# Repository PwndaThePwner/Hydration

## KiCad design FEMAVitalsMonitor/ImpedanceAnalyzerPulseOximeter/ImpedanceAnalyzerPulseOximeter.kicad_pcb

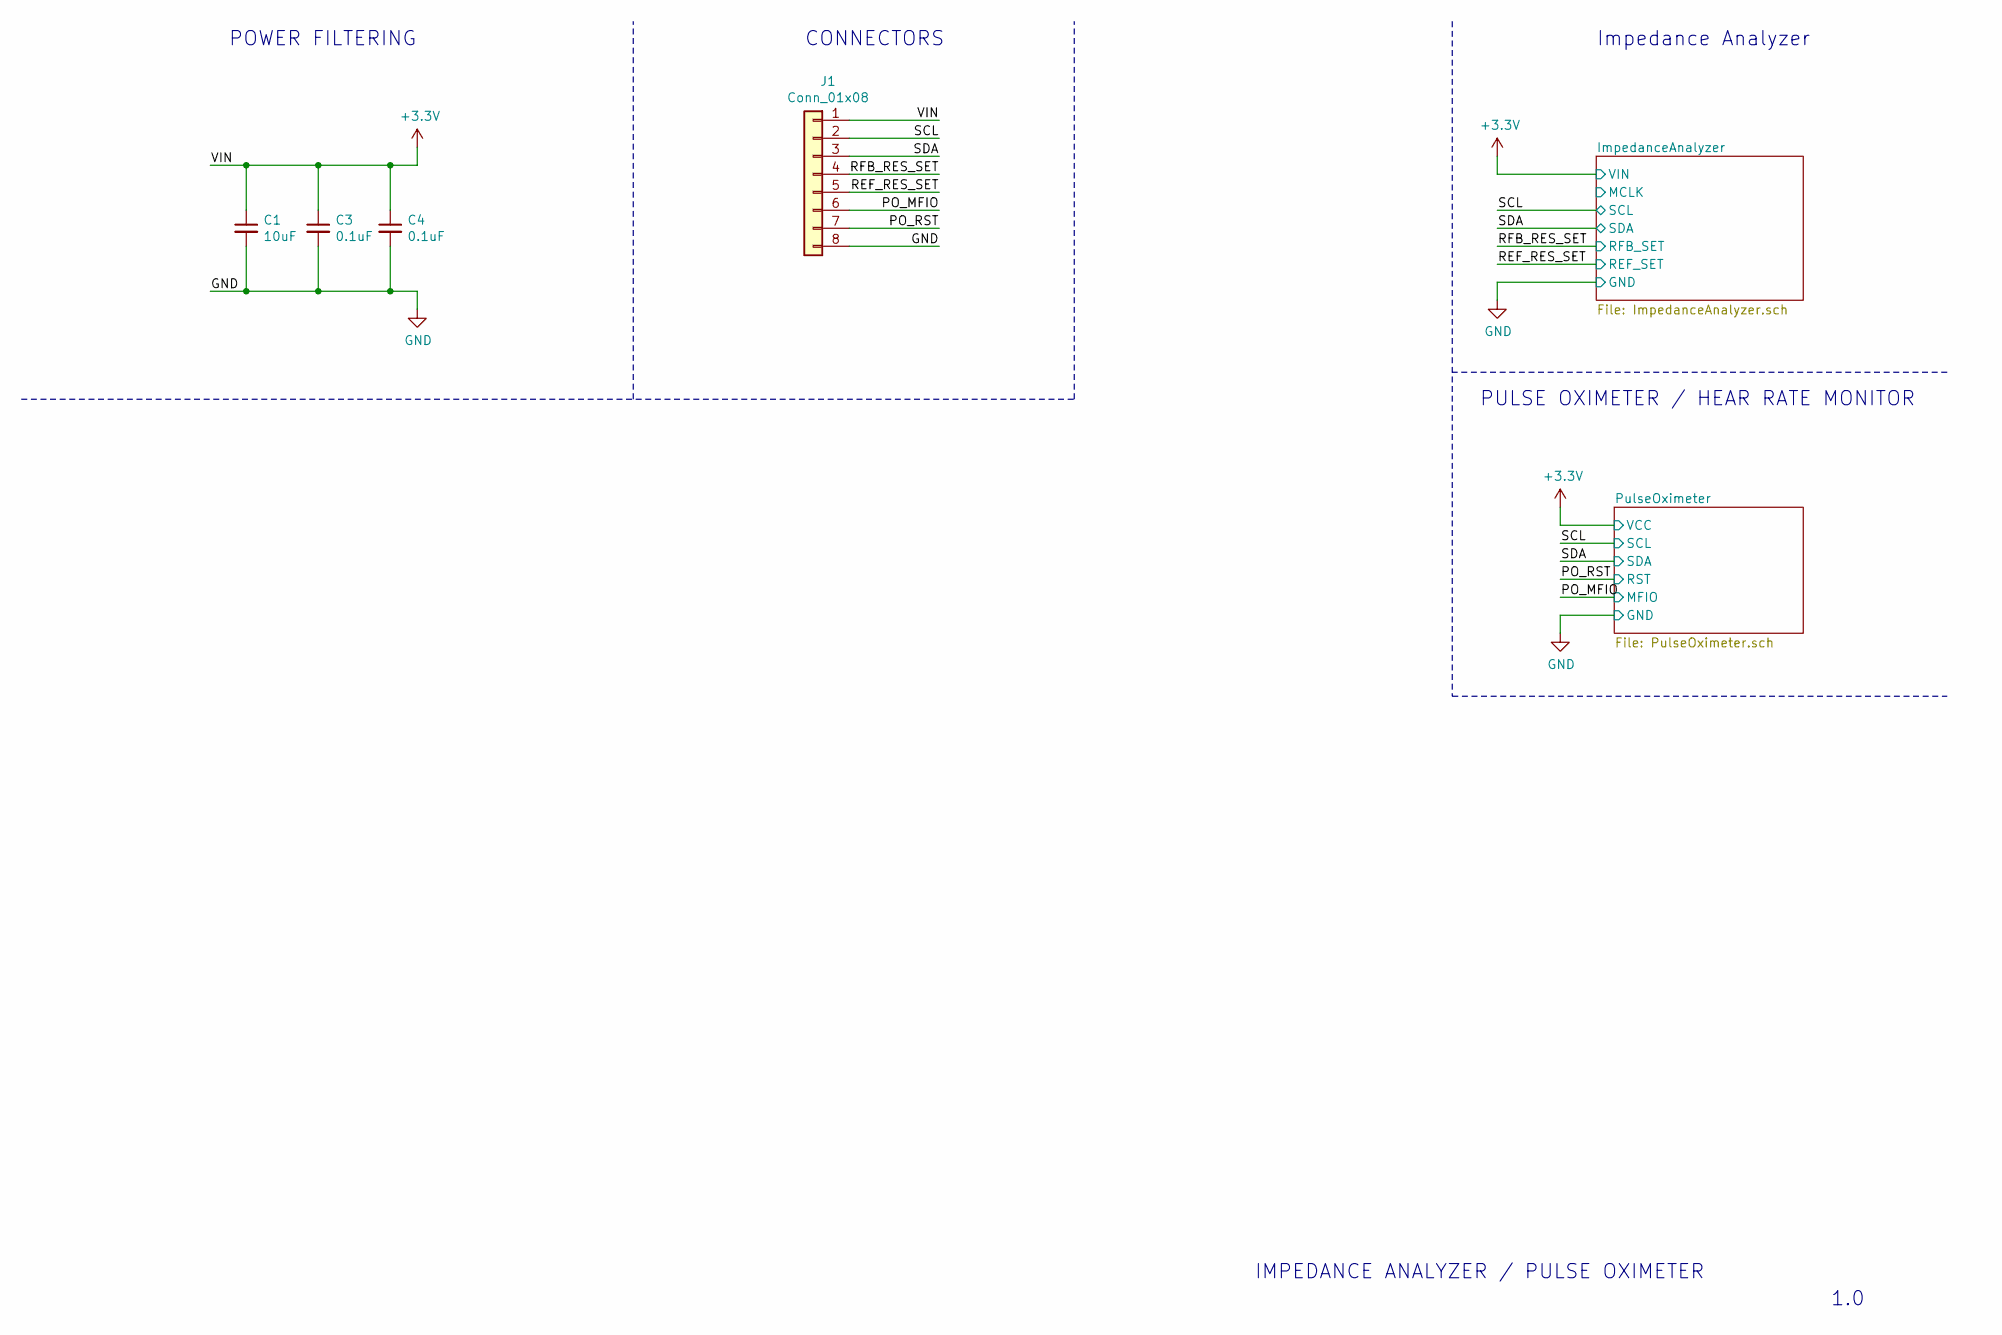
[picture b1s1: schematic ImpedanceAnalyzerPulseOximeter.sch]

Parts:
C1: 10uF; C_0805_2012Metric_Pad1.18x1.45mm_HandSolder
C3, C4: 0.1uF; C_0805_2012Metric_Pad1.18x1.45mm_HandSolder
J1: Conn_01x08; PinHeader_1x08_P2.54mm_Vertical

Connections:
+3V3: C1.1, C3.1, C4.1, J1.1; also elsewhere on the board
/PO_MFIO: J1.6; also elsewhere on the board
/PO_RST: J1.7; also elsewhere on the board
/REF_RES_SET: J1.5; also elsewhere on the board
/RFB_RES_SET: J1.4; also elsewhere on the board
/SCL: J1.2; also elsewhere on the board
/SDA: J1.3; also elsewhere on the board
GND: C1.2, C3.2, C4.2, J1.8; also elsewhere on the board

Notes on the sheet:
Impedance Analyzer
POWER FILTERING
PULSE OXIMETER / HEAR RATE MONITOR
CONNECTORS
IMPEDANCE ANALYZER / PULSE OXIMETER
1.0

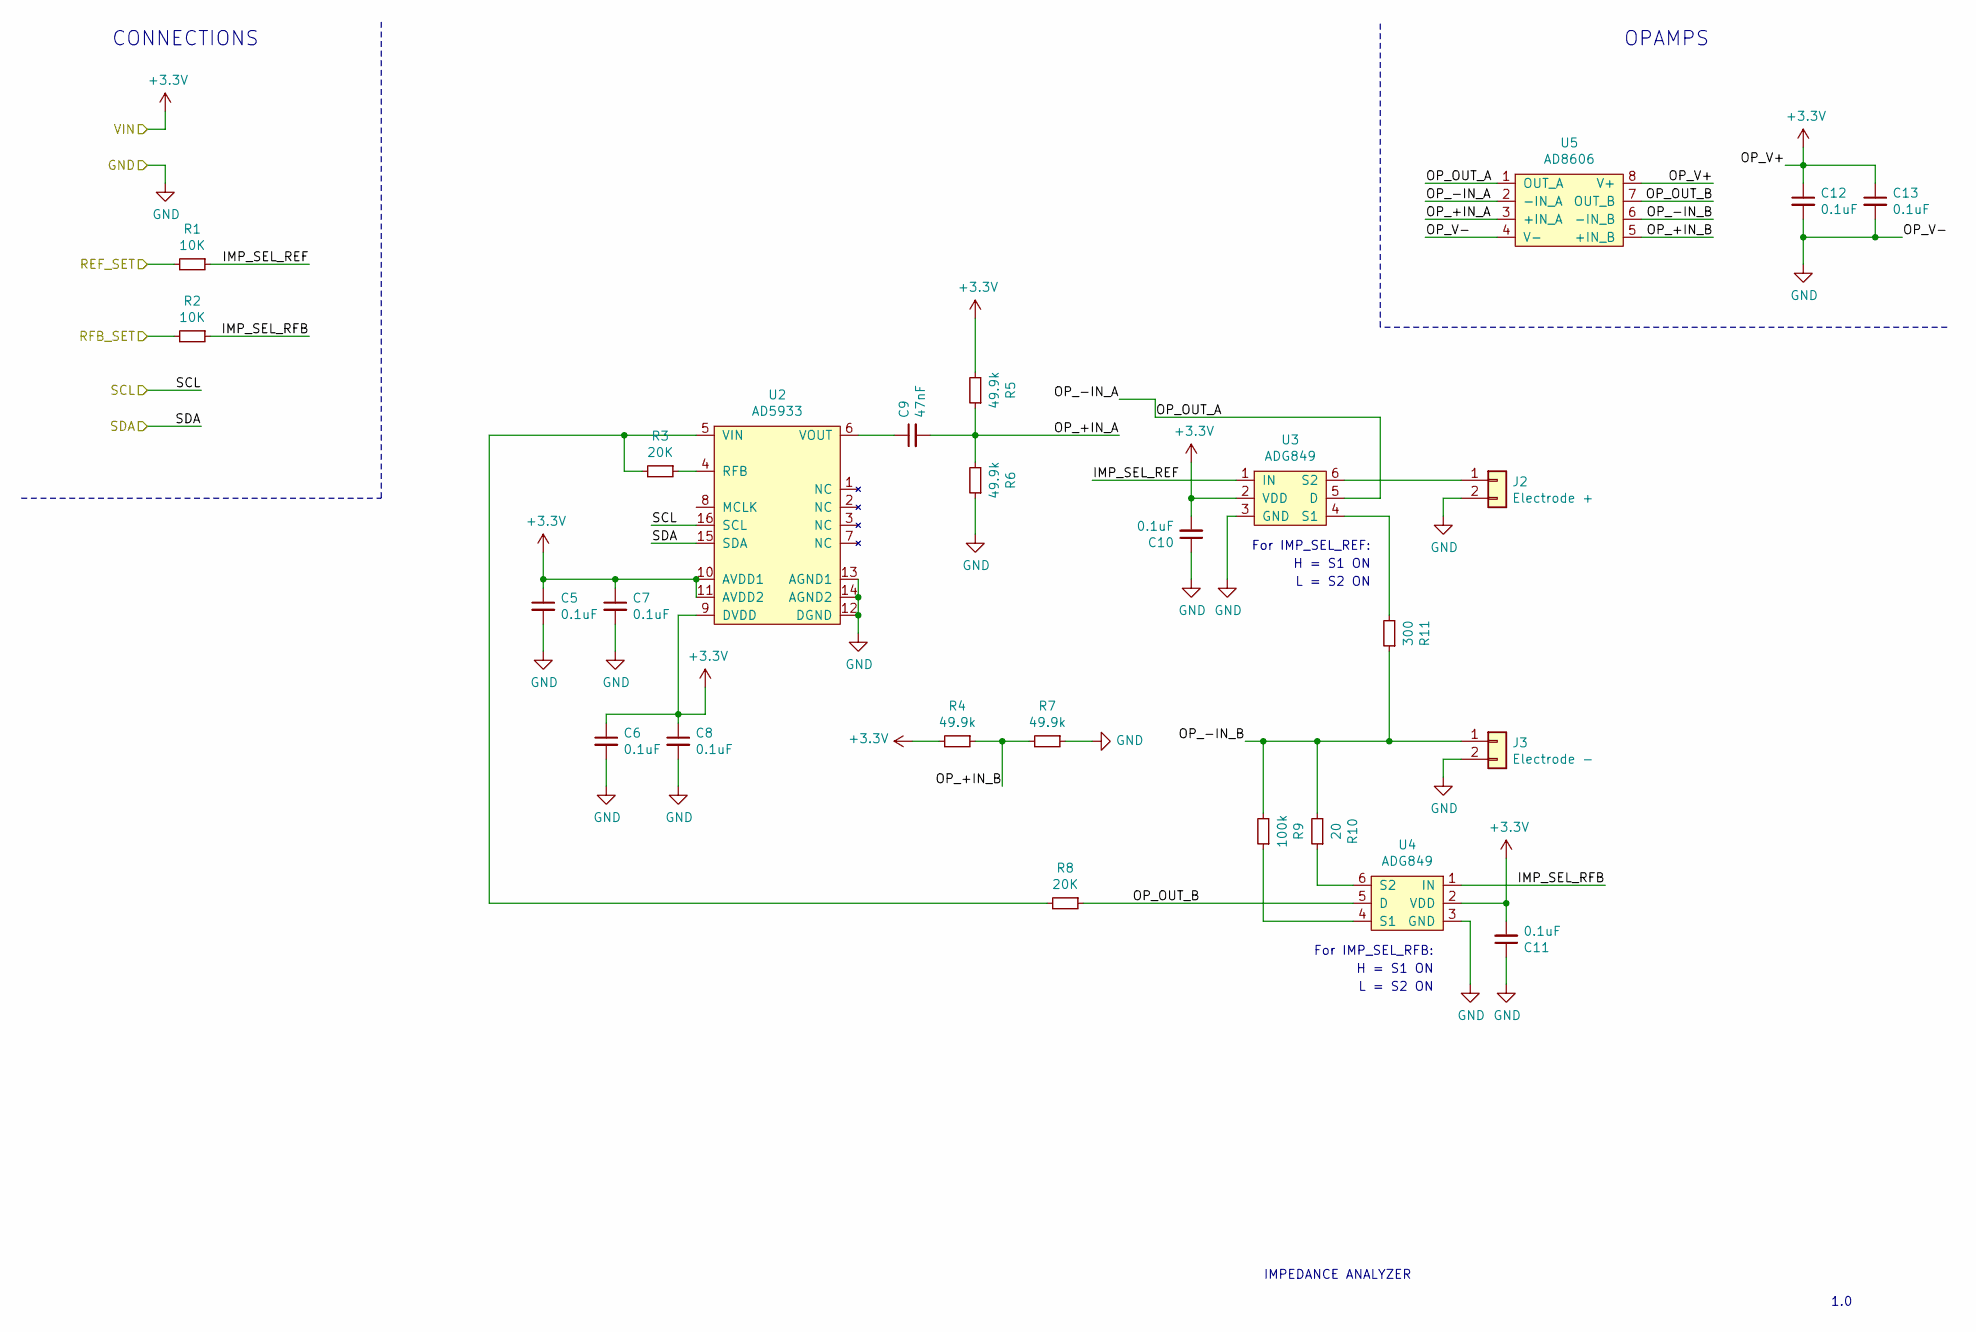
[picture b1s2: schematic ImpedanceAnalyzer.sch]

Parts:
C5, C6, C7, C8, C10, C11, C12, C13: 0.1uF; C_0805_2012Metric_Pad1.18x1.45mm_HandSolder
C9: 47nF; C_0805_2012Metric_Pad1.18x1.45mm_HandSolder
J2: Electrode +; PinHeader_1x02_P2.54mm_Vertical
J3: Electrode -; PinHeader_1x02_P2.54mm_Vertical
R1, R2: 10K; R_0805_2012Metric_Pad1.20x1.40mm_HandSolder
R3, R8: 20K; R_0805_2012Metric_Pad1.20x1.40mm_HandSolder
R4, R5, R6, R7: 49.9k; R_0805_2012Metric_Pad1.20x1.40mm_HandSolder
R9: 100k; R_0805_2012Metric_Pad1.20x1.40mm_HandSolder
R10: 20; R_2010_5025Metric_Pad1.40x2.65mm_HandSolder
R11: 300; R_0805_2012Metric_Pad1.20x1.40mm_HandSolder
U2: AD5933; SSOP-16_5.3x6.2mm_P0.65mm
U3, U4: ADG849
U5: AD8606; MSOP-8_3x3mm_P0.65mm

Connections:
+3V3: C5.1, C6.1, C7.1, C8.1, C10.2, C11.2, C12.1, C13.1, R4.2, R5.2, U2.9 (DVDD), U2.10 (AVDD1), U2.11 (AVDD2), U3.2 (VDD), U4.2 (VDD), U5.8 (V+); also elsewhere on the board
/ImpedanceAnalyzer/IMP_SEL_REF: R1.1, U3.1 (IN)
/ImpedanceAnalyzer/IMP_SEL_RFB: R2.1, U4.1 (IN)
/ImpedanceAnalyzer/OP_+IN_A: C9.2, R5.1, R6.2, U5.3 (+IN_A)
/ImpedanceAnalyzer/OP_+IN_B: R4.1, R7.2, U5.5 (+IN_B)
/ImpedanceAnalyzer/OP_-IN_A: U3.5 (D), U5.1 (OUT_A), U5.2 (-IN_A)
/ImpedanceAnalyzer/OP_-IN_B: J3.1, R9.2, R10.2, R11.1, U5.6 (-IN_B)
/ImpedanceAnalyzer/OP_OUT_B: R8.1, U4.5 (D), U5.7 (OUT_B)
/REF_RES_SET: R1.2; also elsewhere on the board
/RFB_RES_SET: R2.2; also elsewhere on the board
/SCL: U2.16 (SCL); also elsewhere on the board
/SDA: U2.15 (SDA); also elsewhere on the board
GND: C5.2, C6.2, C7.2, C8.2, C10.1, C11.1, C12.2, C13.2, J2.2, J3.2, R6.1, R7.1, U2.12 (DGND), U2.13 (AGND1), U2.14 (AGND2), U3.3 (GND), U4.3 (GND), U5.4 (V-); also elsewhere on the board
unnamed: C9.1, U2.6 (VOUT)
unnamed: J2.1, U3.6 (S2)
unnamed: R3.1, U2.4 (RFB)
unnamed: R3.2, R8.2, U2.5 (VIN)
unnamed: R9.1, U4.4 (S1)
unnamed: R10.1, U4.6 (S2)
unnamed: R11.2, U3.4 (S1)

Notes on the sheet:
For IMP_SEL_REF:
H = S1 ON
L = S2 ON
For IMP_SEL_RFB:
OPAMPS
CONNECTIONS
IMPEDANCE ANALYZER
1.0

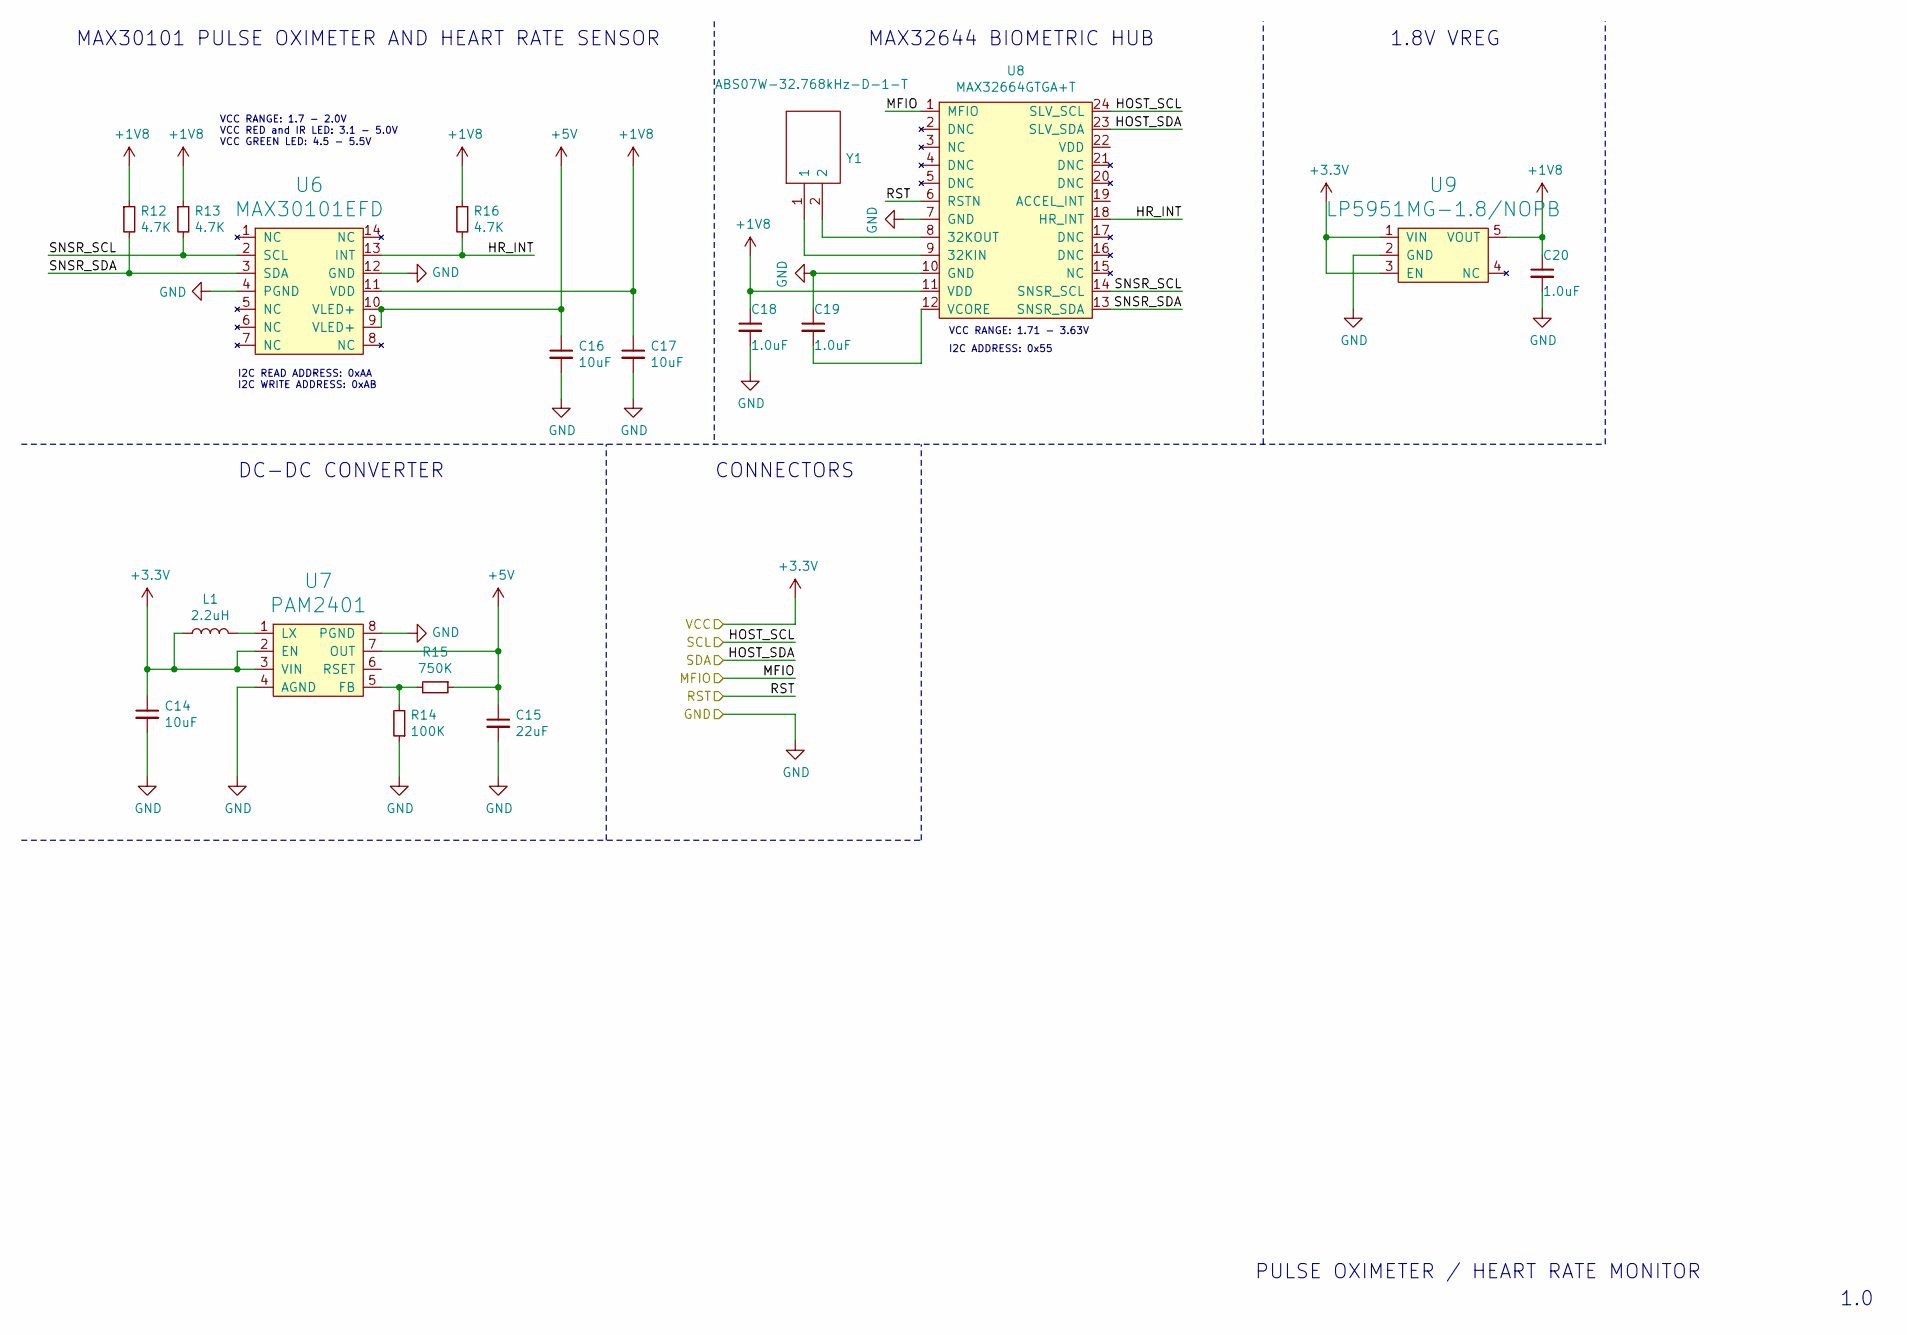
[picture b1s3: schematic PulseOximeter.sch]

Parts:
C14, C16, C17: 10uF; C_0805_2012Metric_Pad1.18x1.45mm_HandSolder
C15: 22uF; C_0805_2012Metric_Pad1.18x1.45mm_HandSolder
C18, C19, C20: 1.0uF; C_0805_2012Metric_Pad1.18x1.45mm_HandSolder
L1: 2.2uH; L_0805_2012Metric_Pad1.15x1.40mm_HandSolder
R12, R13, R16: 4.7K; R_0805_2012Metric_Pad1.20x1.40mm_HandSolder
R14: 100K; R_0805_2012Metric_Pad1.20x1.40mm_HandSolder
R15: 750K; R_0805_2012Metric_Pad1.20x1.40mm_HandSolder
U6: MAX30101EFD; 14-LEAD-OESIP
U7: PAM2401; MSOP-8_3x3mm_P0.65mm
U8: MAX32664GTGA+T; MAX32664GTGA&plus_T
U9: LP5951MG-1.8/NOPB; SOT-353_SC-70-5_Handsoldering
Y1: ABS07W-32.768kHz-D-1-T; ABS07AIG32768kHz71T; Mouser Part Number 815-ABS07W32.768KD1T

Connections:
+1V8: C17.1, C18.1, C20.1, R12.1, R13.1, R16.1, U6.11 (VDD), U8.11 (VDD), U9.5 (VOUT)
+3V3: C14.1, L1.1, U7.2 (EN), U7.3 (VIN), U9.1 (VIN), U9.3 (EN); also elsewhere on the board
+5V: C15.1, C16.1, R15.1, U6.9 (VLED+), U6.10 (VLED+), U7.7 (OUT)
/PO_MFIO: U8.1 (MFIO); also elsewhere on the board
/PO_RST: U8.6 (RSTN); also elsewhere on the board
/PulseOximeter/HR_INT: R16.2, U6.13 (INT), U8.18 (HR_INT)
/PulseOximeter/SNSR_SCL: R13.2, U6.2 (SCL), U8.14 (SNSR_SCL)
/PulseOximeter/SNSR_SDA: R12.2, U6.3 (SDA), U8.13 (SNSR_SDA)
/SCL: U8.24 (SLV_SCL); also elsewhere on the board
/SDA: U8.23 (SLV_SDA); also elsewhere on the board
GND: C14.2, C15.2, C16.2, C17.2, C18.2, C19.1, C20.2, R14.1, U6.4 (PGND), U6.12 (GND), U7.4 (AGND), U7.8 (PGND), U8.7 (GND), U8.10 (GND), U9.2 (GND); also elsewhere on the board
unnamed: C19.2, U8.12 (VCORE)
unnamed: L1.2, U7.1 (LX)
unnamed: R14.2, R15.2, U7.5 (FB)
unnamed: U8.8 (32KOUT), Y1.2
unnamed: U8.9 (32KIN), Y1.1

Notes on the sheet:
MAX30101 PULSE OXIMETER AND HEART RATE SENSOR
I2C READ ADDRESS: 0xAA I2C WRITE ADDRESS: 0xAB
VCC RANGE: 1.7 - 2.0V VCC RED and IR LED: 3.1 - 5.0V VCC GREEN LED: 4.5 - 5.5V
I2C ADDRESS: 0x55
VCC RANGE: 1.71 - 3.63V
MAX32644 BIOMETRIC HUB
1.8V VREG
DC-DC CONVERTER
CONNECTORS
PULSE OXIMETER / HEART RATE MONITOR
1.0

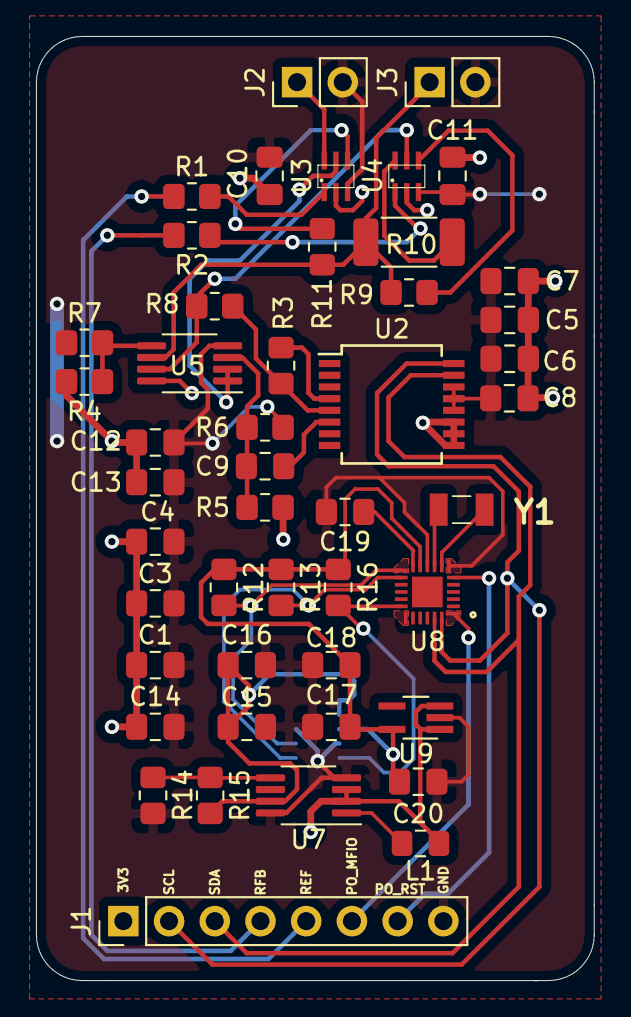
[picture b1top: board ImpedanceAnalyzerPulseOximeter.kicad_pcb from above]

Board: 2 copper layers, 31.0 x 52.5 mm, 48 parts (1 on the bottom side), 32 nets.

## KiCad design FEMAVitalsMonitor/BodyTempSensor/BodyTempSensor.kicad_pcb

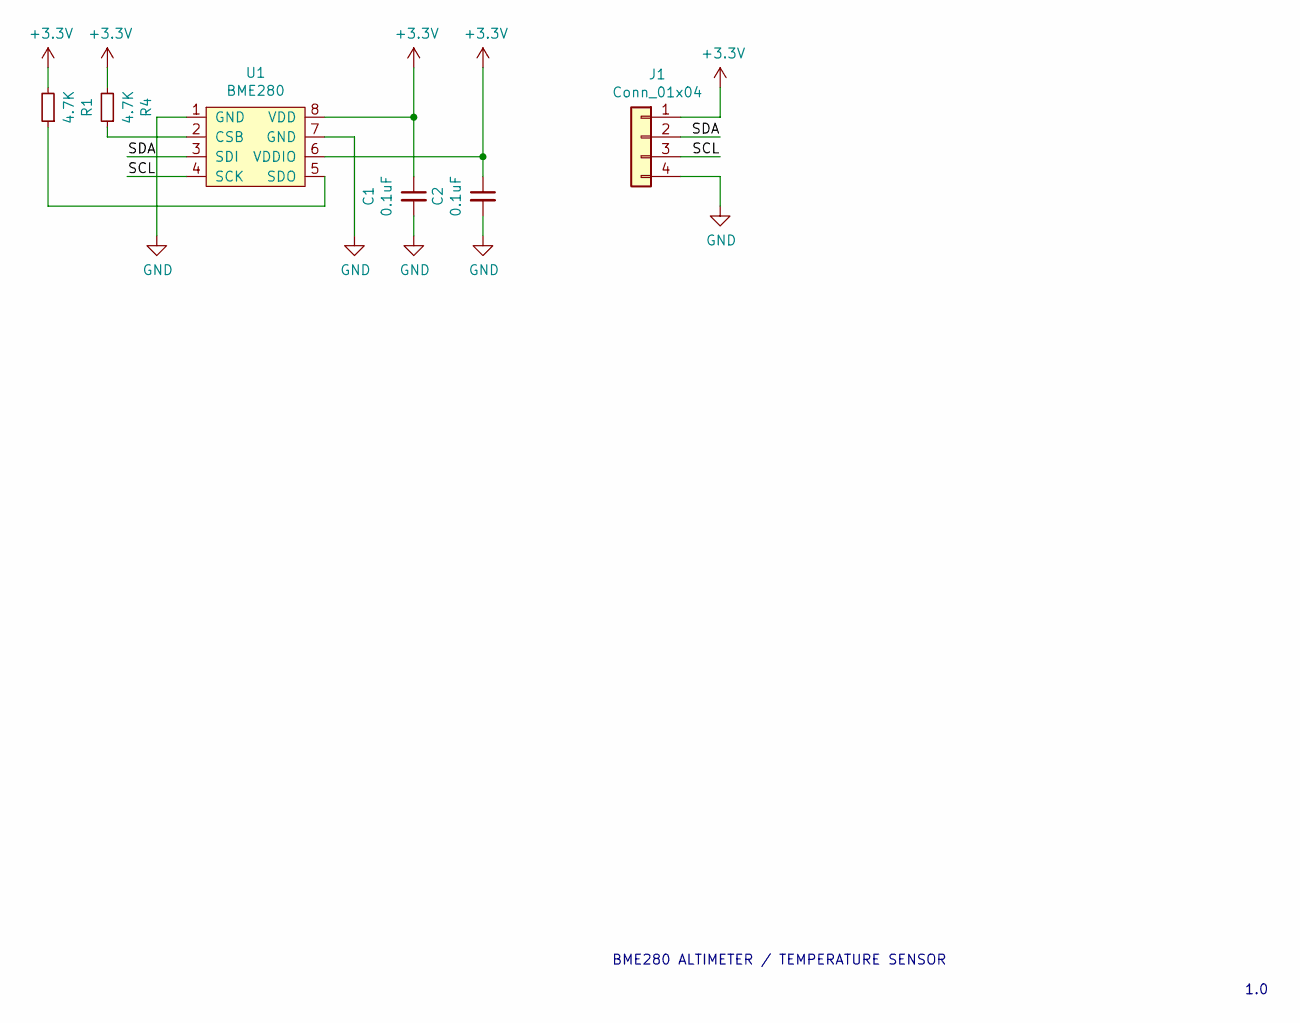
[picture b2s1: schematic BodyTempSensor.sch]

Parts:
C1, C2: 0.1uF; C_0805_2012Metric_Pad1.18x1.45mm_HandSolder
J1: Conn_01x04; PinHeader_1x04_P2.54mm_Vertical
R1, R4: 4.7K; R_0805_2012Metric_Pad1.20x1.40mm_HandSolder
U1: BME280; BMP280

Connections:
+3V3: C1.1, C2.1, J1.1, R1.2, R4.2, U1.6 (VDDIO), U1.8 (VDD)
/SCL: J1.3, U1.4 (SCK)
/SDA: J1.2, U1.3 (SDI)
GND: C1.2, C2.2, J1.4, U1.1 (GND), U1.7 (GND)
unnamed: R1.1, U1.5 (SDO)
unnamed: R4.1, U1.2 (CSB)

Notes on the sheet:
BME280 ALTIMETER / TEMPERATURE SENSOR
1.0

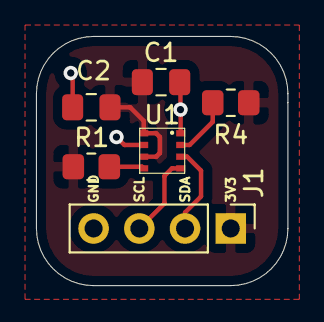
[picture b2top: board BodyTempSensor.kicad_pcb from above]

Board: 2 copper layers, 14.0 x 13.8 mm, 6 parts (0 on the bottom side), 6 nets.

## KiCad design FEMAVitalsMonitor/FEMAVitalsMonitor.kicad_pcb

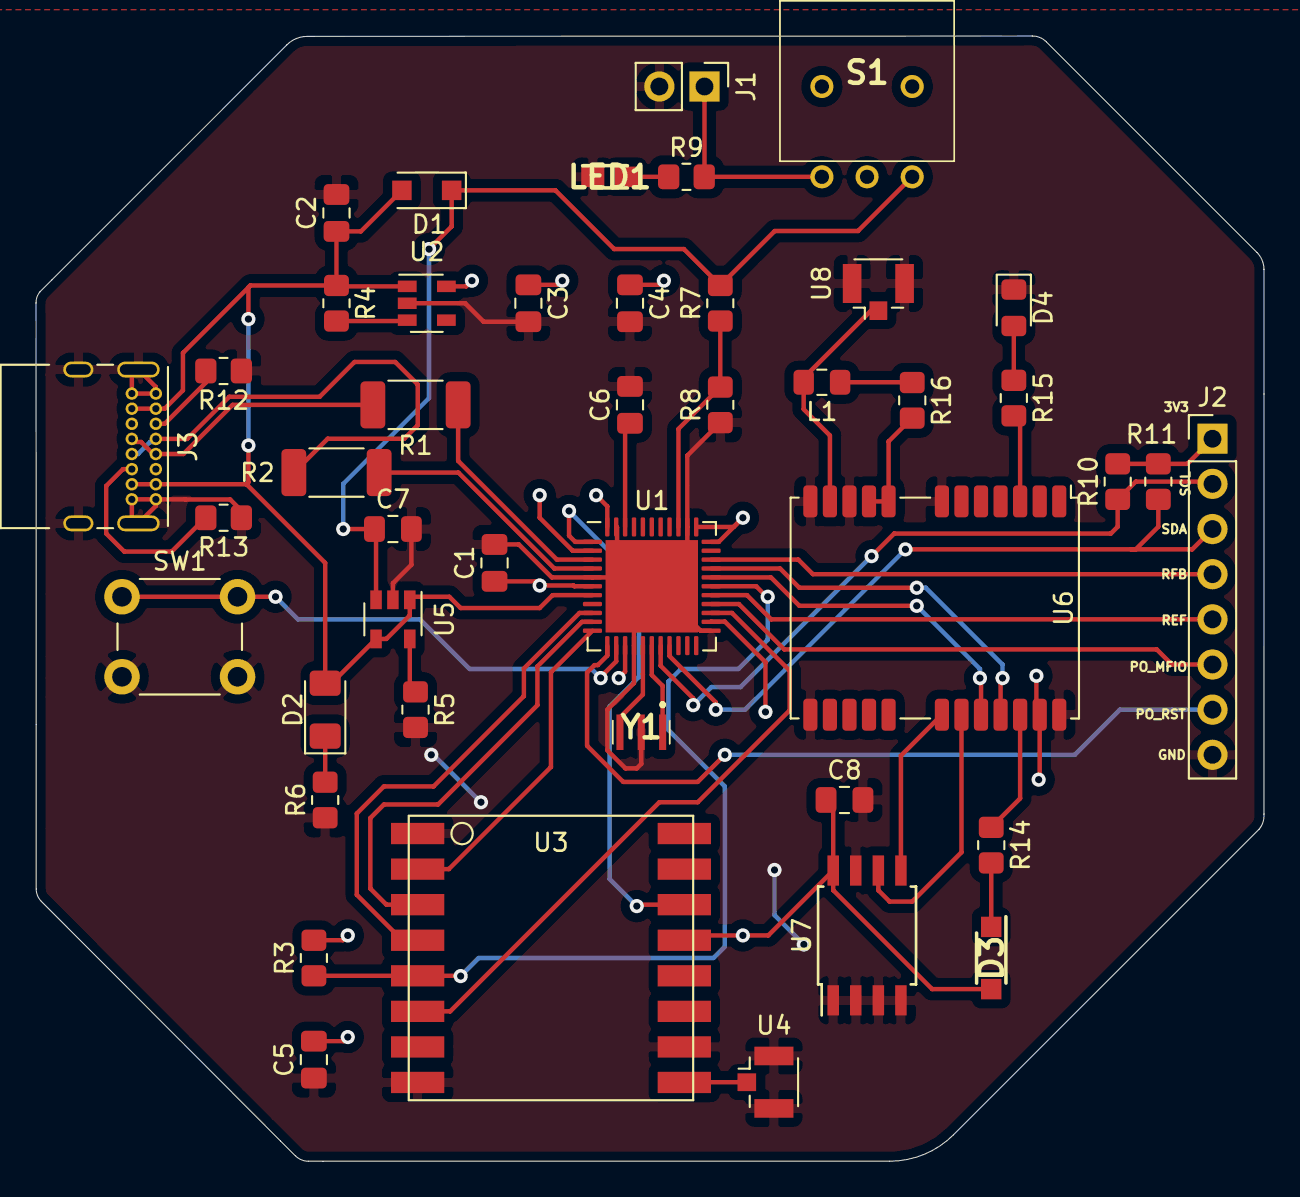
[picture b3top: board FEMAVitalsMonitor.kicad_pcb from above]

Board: 2 copper layers, 69.1 x 63.3 mm, 44 parts (0 on the bottom side), 44 nets.

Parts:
C1, C6: 1uF; C_0805_2012Metric_Pad1.18x1.45mm_HandSolder
C2, C3, C4, C5, C7: 10uF; C_0805_2012Metric_Pad1.18x1.45mm_HandSolder
C8: 0.1uF; C_0805_2012Metric_Pad1.18x1.45mm_HandSolder
D1: MBR120; D_SOD-123F
D2: LED; LED_1206_3216Metric_Pad1.42x1.75mm_HandSolder
D3: SM5817PL-TP; SOD3716X120N
D4: FIX; LED_0805_2012Metric_Pad1.15x1.40mm_HandSolder
J1: Battery; PinHeader_1x02_P2.54mm_Vertical
J2: Conn_01x08; PinHeader_1x08_P2.54mm_Vertical
J3: USB_C_Receptacle_USB2.0; USB_C_Receptacle_GCT_USB4085
L1: 22uH; L_0805_2012Metric_Pad1.15x1.40mm_HandSolder
LED1: APTD2012LSURCK; LEDM2012X120N
R1, R2: 22; R_2010_5025Metric_Pad1.40x2.65mm_HandSolder
R3, R4, R7, R8: 100K; R_0805_2012Metric_Pad1.20x1.40mm_HandSolder
R5: 10K; R_0805_2012Metric_Pad1.20x1.40mm_HandSolder
R6, R14, R15: 1K; R_0805_2012Metric_Pad1.20x1.40mm_HandSolder
R9: 1.47k; R_0805_2012Metric_Pad1.20x1.40mm_HandSolder
R10, R11: 4.7k; R_0805_2012Metric_Pad1.20x1.40mm_HandSolder
R12, R13: 5.1k; R_0805_2012Metric_Pad1.20x1.40mm_HandSolder
R16: 22; R_0805_2012Metric_Pad1.20x1.40mm_HandSolder
S1: AS11AH; AS13AH
SW1: SW_DIP_x01; SW_PUSH_6mm_H7.3mm
U1: ATmega32U4-MU; QFN-44-1EP_7x7mm_P0.5mm_EP5.2x5.2mm
U2: AP2112K-3.3; SOT-23-5
U3: RFM69HCW
U4: uFL; U.FL_Hirose_U.FL-R-SMT-1_Vertical
U5: MCP73831-2-OT; SOT-23-5
U6: NEO-M8; ublox_NEO
U7: 24AA32A; SOIJ-8_5.3x5.3mm_P1.27mm
U8: uFLConnector; U.FL_Hirose_U.FL-R-SMT-1_Vertical
Y1: 8MHz; AWSCR800CELBC10T3

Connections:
+3V3: C1.1, C3.1, C4.1, C5.2, C8.1, D3.2, J2.1, R3.2, R10.2, R11.2, U1.2, U1.6, U1.14, U1.24, U1.33, U1.34, U1.44, U2.5, U3.13, U6.23, U7.8
+BATT: C7.1, D1.1, R7.2, S1.1, U5.3
/A0: R7.1, R8.2, U1.36
/AREF: C6.1, U1.42
/D+: R2.1, U1.4
/D-: R1.1, U1.3
/DIO0: U1.1, U3.14
/GPS_RX: U1.30, U6.21
/GPS_TX: U1.29, U6.20
/LORA_NSS: R3.1, U1.28, U3.5
/LORA_RST: U1.25, U3.6
/MISO: U1.11, U3.2
/MOSI: U1.10, U3.3
/NEO-M8 GPS/SCL: U6.19, U7.6
/NEO-M8 GPS/SDA: U6.18, U7.5
/PO_MFIO: J2.6, U1.26
/PO_RST: J2.7, U1.12
/REF_RES_SET: J2.5, U1.27
/RFB_RES_SET: J2.4, U1.31
/RST: SW1.1, U1.13
/SCK: U1.9, U3.4
/SCL: J2.2, R10.1, U1.18
/SDA: J2.3, R11.1, U1.19
GND: C1.2, C2.2, C3.2, C4.2, C5.1, C6.2, C7.2, C8.2, D4.1, J1.2, J2.8, J3.A1, J3.A12, J3.B1, J3.B12, J3.S1, LED1.1, R5.2, R6.1, R8.1, R12.1, R13.1, SW1.2, U1.5, U1.15, U1.23, U1.35, U1.43, U1.45, U2.2, U3.1, U3.8, U3.10, U4.2, U5.2, U6.7, U6.10, U6.12, U6.13, U6.24, U7.1, U7.2, U7.3, U7.4, U7.7, U8.2, Y1.2
unnamed: D2.1, R6.2
unnamed: D3.1, R14.2
unnamed: D4.2, R15.1
unnamed: J1.1, R9.2, S1.3
unnamed: J3.A5, R12.2
unnamed: J3.A6, J3.B6, R2.2
unnamed: J3.A7, J3.B7, R1.2
unnamed: J3.B5, R13.2
unnamed: L1.1, R16.1
unnamed: L1.2, U6.11, U8.1
unnamed: LED1.2, R9.1
unnamed: R4.2, U2.3
unnamed: R5.1, U5.5
unnamed: R14.1, U6.22
unnamed: R15.2, U6.3
unnamed: R16.2, U6.8, U6.9
unnamed: U1.16, Y1.3
unnamed: U1.17, Y1.1
unnamed: U3.9, U4.1
VBUS: C2.1, D1.2, D2.2, J3.A4, J3.A9, J3.B4, J3.B9, R4.1, U1.7, U2.1, U5.1, U5.4

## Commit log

2021-02-24 version 1
2021-02-25 file
2021-02-25 test
2021-02-25 main function
2021-02-25 white paper from drive
2021-02-27 inventory 2/26
2021-03-02 Updated Inventory w/ PCB Inventories
2021-03-02 update 3/2
2021-03-02 updated w volt regulator missing on MCU PCB
2021-03-04 3/4 Update
2021-03-04 3/4: Available MCUs, info, and concerns
2021-03-09 3/9 update
2021-03-11 3/10 Update
2021-03-11 PCB Design Projects 3/11/21
2021-03-15 3/15
2021-03-15 3/15: no atmega32u4-MU yet
2021-03-16 Battery Candidates 3/16
2021-03-16 3/16
2021-03-18 3/18
2021-03-19 3/19
2021-03-22 3/22
2021-03-23 3/23
2021-03-24 3/24
2021-03-25 3/25
2021-03-31 3/31
2021-04-15 4/15
2021-04-16 4/16
2021-04-22 4/22
2021-04-23 4/23
2021-04-29 4/29
2021-04-30 4/30
2021-05-12 5/12
2021-05-14 5/14
2021-07-08 code
